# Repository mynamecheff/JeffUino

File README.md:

# Name In Progress
mcu board I'm making

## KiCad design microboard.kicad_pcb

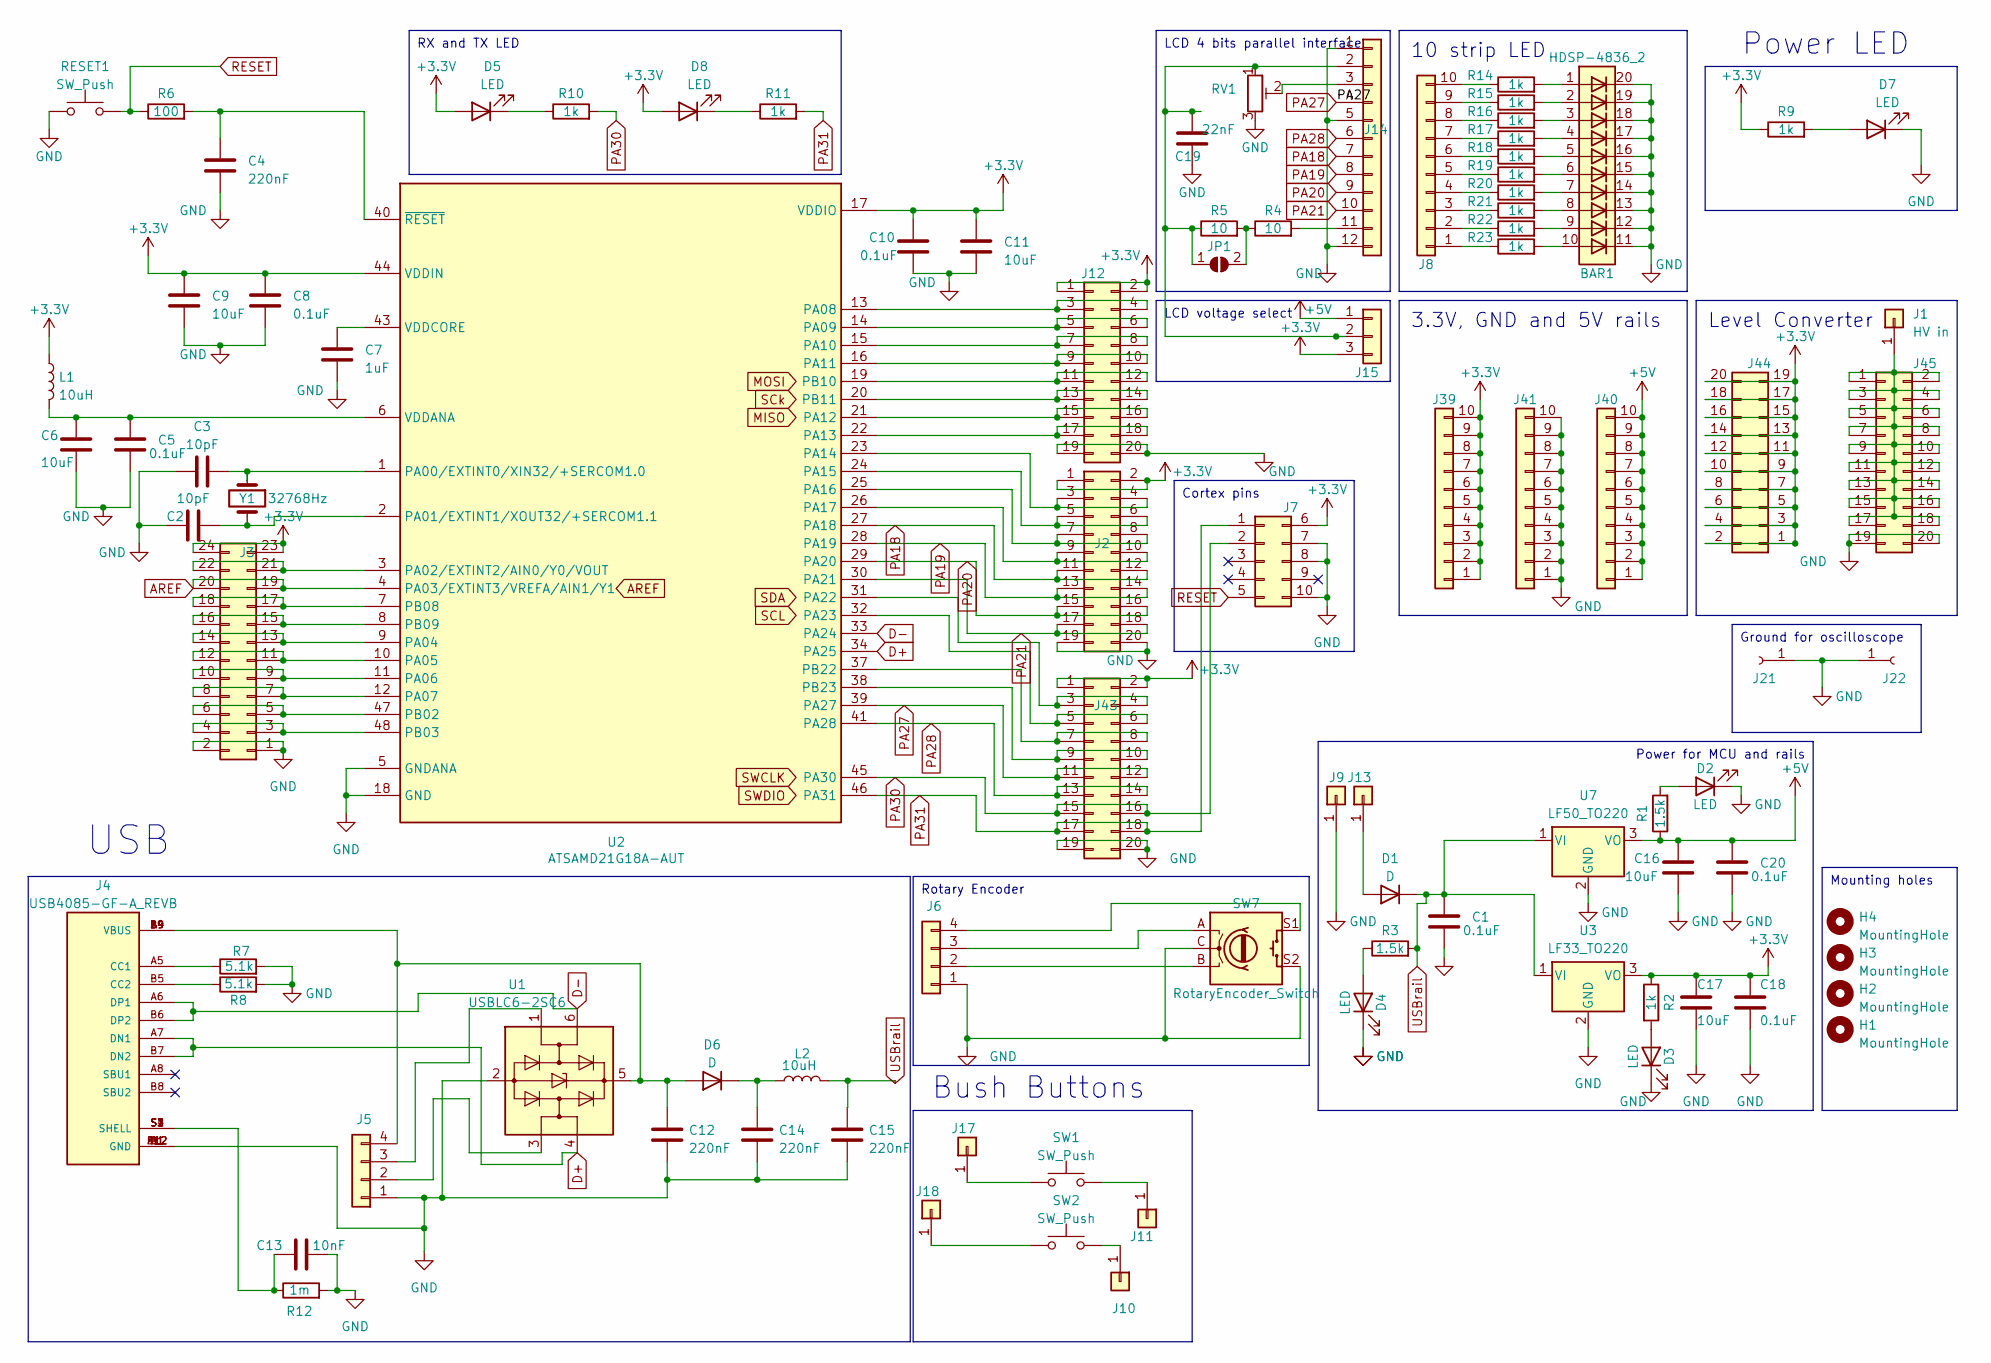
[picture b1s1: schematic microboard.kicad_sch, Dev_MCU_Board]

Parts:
BAR1: HDSP-4836_2; HDSP-4836
C1, C5, C8, C10, C18, C20: 0.1uF; C_0805_2012Metric_Pad1.18x1.45mm_HandSolder
C2, C3: 10pF; C_0805_2012Metric_Pad1.18x1.45mm_HandSolder
C4, C12, C14, C15: 220nF; C_0805_2012Metric_Pad1.18x1.45mm_HandSolder
C6, C9, C11, C16, C17: 10uF; C_0805_2012Metric_Pad1.18x1.45mm_HandSolder
C7: 1uF; C_0805_2012Metric_Pad1.18x1.45mm_HandSolder
C13: 10nF; C_0805_2012Metric_Pad1.18x1.45mm_HandSolder
C19: 22nF; C_0805_2012Metric_Pad1.18x1.45mm_HandSolder
D1, D6: D; D_SOD-323_HandSoldering
D2, D3, D4, D5, D7, D8: LED; LED_0805_2012Metric_Pad1.15x1.40mm_HandSolder
H1, H2, H3, H4: MountingHole; MountingHole_3.2mm_M3
J1: HV in; PinHeader_1x01_P2.54mm_Vertical
J2, J12: Conn_01x10; PinHeader_2x10_P2.54mm_Vertical
J3: Conn_02x12; PinHeader_2x12_P2.54mm_Vertical
J4: USB4085-GF-A_REVB; GCT_USB4085-GF-A_REVB; PARTREV B
J5, J6: Conn_01x04; PinHeader_1x04_P2.54mm_Vertical
J7: Conn_01x05; PinHeader_2x05_P1.27mm_Vertical
J8, J39, J40, J41: Conn_01x10; PinHeader_1x10_P2.54mm_Vertical
J9, J10, J11, J13, J17, J18: Conn_01x01; PinHeader_1x01_P2.54mm_Vertical
J14: Conn_01x12; PinHeader_1x12_P2.54mm_Vertical
J15: Conn_01x03; PinHeader_1x03_P2.54mm_Vertical
J21, J22: Conn_01x01_Socket; PinHeader_1x01_P2.54mm_Vertical
J43: Conn_01x05; PinHeader_2x10_P2.54mm_Vertical
J44: Conn_01x09; PinHeader_2x10_P2.54mm_Vertical
J45: Conn_01x08; PinHeader_2x10_P2.54mm_Vertical
JP1: SolderJumper_2_Open; SolderJumper-2_P1.3mm_Open_RoundedPad1.0x1.5mm
L1, L2: 10uH; L_0805_2012Metric_Pad1.05x1.20mm_HandSolder
R1, R3: 1.5k; R_0805_2012Metric_Pad1.20x1.40mm_HandSolder
R2, R9, R10, R11, R14, R15, R16, R17, R18, R19, R20, R21, R22, R23: 1k; R_0805_2012Metric_Pad1.20x1.40mm_HandSolder
R4, R5: 10; R_0805_2012Metric_Pad1.20x1.40mm_HandSolder
R6: 100; R_0805_2012Metric_Pad1.20x1.40mm_HandSolder
R7, R8: 5.1k; R_0805_2012Metric_Pad1.20x1.40mm_HandSolder
R12: 1m; R_0805_2012Metric_Pad1.20x1.40mm_HandSolder
RESET1: SW_Push; SW_PUSH_6mm_H8mm
RV1: R_Potentiometer_Trim; Potentiometer_Runtron_RM-065_Vertical
SW1, SW2: SW_Push; SW_PUSH_6mm_H8mm
SW7: RotaryEncoder_Switch; RotaryEncoder_Alps_EC11E-Switch_Vertical_H20mm
U1: USBLC6-2SC6; SOT-23-6
U2: ATSAMD21G18A-AUT; TQFP-48_7x7mm_P0.5mm_hand_solder; MPN ATSAMD21G18A-AUT
U3: LF33_TO220; TO-220-3_Vertical
U7: LF50_TO220; TO-220-3_Vertical
Y1: 32768Hz; Crystal_SMD_G8-2Pin_3.2x1.5mm_HandSoldering

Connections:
+3.3V: C8.1, C9.1, C10.1, C11.1, C17.1, C18.1, D5.2 (A), D8.2 (A), J2.1, J2.2, J3.23, J3.24, J7.6, J12.1, J12.2, J15.3, J39.1, J39.2, J39.3, J39.4, J39.5, J39.6, J39.7, J39.8, J39.9, J39.10, J43.1, J43.2, J44.1, J44.2, J44.3, J44.4, J44.5, J44.6, J44.7, J44.8, J44.9, J44.10, J44.11, J44.12, J44.13, J44.14, J44.15, J44.16, J44.17, J44.18, J44.19, J44.20, L1.1, R2.1, R9.1, U2.17 (VDDIO), U2.36 (VDDIO), U2.44 (VDDIN), U3.3 (VO); also elsewhere on the board
+5V: C16.1, C20.1, J15.1, J40.1, J40.2, J40.3, J40.4, J40.5, J40.6, J40.7, J40.8, J40.9, J40.10, R1.1, U7.3 (VO)
AREF: J3.19, J3.20, U2.4 (PA03/EXTINT3/VREFA/AIN1/Y1)
D+: J4.A7 (DN1), J4.B7 (DN2), U1.4 (I/O2), U2.34 (PA25)
D-: J4.A6 (DP1), J4.B6 (DP2), U1.6 (I/O1), U2.33 (PA24)
GND: BAR1.11 (K), BAR1.12 (K), BAR1.13 (K), BAR1.14 (K), BAR1.15 (K), BAR1.16 (K), BAR1.17 (K), BAR1.18 (K), BAR1.19 (K), BAR1.20 (K), C1.2, C2.1, C3.2, C4.2, C5.2, C6.2, C7.2, C8.2, C9.2, C10.2, C11.2, C12.2, C13.2, C14.2, C15.2, C16.2, C17.2, C18.2, C19.2, C20.2, D2.1 (K), D3.1 (K), D4.1 (K), D7.1 (K), J2.19, J2.20, J3.1, J3.2, J4.A1 (GND), J4.A12 (GND), J4.B1 (GND), J4.B12 (GND), J5.1, J6.1, J7.7, J7.8, J7.10, J9.1, J12.19, J12.20, J14.1, J14.5, J14.12, J21.1, J22.1, J41.1, J41.2, J41.3, J41.4, J41.5, J41.6, J41.7, J41.8, J41.9, J41.10, J43.19, J43.20, J45.19, J45.20, R7.2, R8.2, R12.2, RESET1.1, RV1.3, SW7.C, SW7.S2, U1.2 (GND), U2.5 (GNDANA), U2.18 (GND), U2.35 (GND), U2.42 (GND), U3.2 (GND), U7.2 (GND); also elsewhere on the board
unnamed: BAR1.1 (A), R14.2
unnamed: BAR1.2 (A), R15.2
unnamed: BAR1.3 (A), R16.2
unnamed: BAR1.4 (A), R17.2
unnamed: BAR1.5 (A), R18.2
unnamed: BAR1.6 (A), R19.2
unnamed: BAR1.7 (A), R20.2
unnamed: BAR1.8 (A), R21.2
unnamed: BAR1.9 (A), R22.2
unnamed: BAR1.10 (A), R23.2
unnamed: C13.1, J4.S1 (SHELL), J4.S2 (SHELL), J4.S3 (SHELL), J4.S4 (SHELL), R12.1
unnamed: D1.2 (A), J13.1
unnamed: D2.2 (A), R1.2
unnamed: D3.2 (A), R2.2
unnamed: D4.2 (A), R3.1
unnamed: D5.1 (K), R10.1
unnamed: C12.1, D6.2 (A), J4.A4 (VBUS), J4.A9 (VBUS), J4.B4 (VBUS), J4.B9 (VBUS), J5.4, U1.5 (VBUS)
unnamed: C14.1, D6.1 (K), L2.2
unnamed: D7.2 (A), R9.2
unnamed 26: D8.1 (K), R11.1; also elsewhere on the board
unnamed: J1.1, J45.1, J45.2, J45.3, J45.4, J45.5, J45.6, J45.7, J45.8, J45.9, J45.10, J45.11, J45.12, J45.13, J45.14, J45.15, J45.16, J45.17, J45.18
unnamed: J2.3, J2.4, U2.23 (PA14)
unnamed: J2.5, J2.6, U2.24 (PA15)
unnamed: J2.7, J2.8, U2.25 (PA16)
unnamed: J2.9, J2.10, U2.26 (PA17)
unnamed: J3.3, J3.4, U2.48 (PB03)
unnamed: J3.5, J3.6, U2.47 (PB02)
unnamed: J3.7, J3.8, U2.12 (PA07)
unnamed: J3.9, J3.10, U2.11 (PA06)
unnamed: J3.11, J3.12, U2.10 (PA05)
unnamed: J3.13, J3.14, U2.9 (PA04)
unnamed: J3.15, J3.16, U2.8 (PB09)
unnamed: J3.17, J3.18, U2.7 (PB08)
unnamed: J3.21, J3.22, U2.3 (PA02/EXTINT2/AIN0/Y0/VOUT)
unnamed: J4.A5 (CC1), R7.1
unnamed: J4.B5 (CC2), R8.1
unnamed: J5.2, U1.3 (I/O2)
unnamed: J5.3, U1.1 (I/O1)
unnamed: J6.2, SW7.B
unnamed: J6.3, SW7.A
unnamed: J6.4, SW7.S1
unnamed: J8.1, R23.1
unnamed: J8.2, R22.1
unnamed: J8.3, R21.1
unnamed: J8.4, R20.1
unnamed: J8.5, R19.1
unnamed: J8.6, R18.1
unnamed: J8.7, R17.1
unnamed: J8.8, R16.1
unnamed: J8.9, R15.1
unnamed: J8.10, R14.1
unnamed: J10.1, SW2.2
unnamed: J11.1, SW1.2
unnamed: J12.3, J12.4, U2.13 (PA08)
unnamed: J12.5, J12.6, U2.14 (PA09)
unnamed: J12.7, J12.8, U2.15 (PA10)
unnamed: J12.9, J12.10, U2.16 (PA11)
unnamed: J12.11, J12.12, U2.19 (PB10)
unnamed: J12.13, J12.14, U2.20 (PB11)
unnamed 66: J12.15, J12.16, U2.21 (PA12); also elsewhere on the board
unnamed: J12.17, J12.18, U2.22 (PA13)
unnamed: C19.1, J14.2, J15.2, JP1.1 (A), R5.1, RV1.1
unnamed: J14.3, RV1.2
unnamed: J14.11, R4.2
unnamed: J17.1, SW1.1
unnamed: J18.1, SW2.1
unnamed: J43.3, J43.4, U2.31 (PA22)
unnamed: J43.5, J43.6, U2.32 (PA23)
unnamed: J43.7, J43.8, U2.37 (PB22)
unnamed: J43.9, J43.10, U2.38 (PB23)
unnamed: JP1.2 (B), R4.1, R5.2
unnamed: C3.1, U2.1 (PA00/EXTINT0/XIN32/+SERCOM1.0), Y1.1
unnamed: C2.2, U2.2 (PA01/EXTINT1/XOUT32/+SERCOM1.1), Y1.2
unnamed: C5.1, C6.1, L1.2, U2.6 (VDDANA)
unnamed: C7.1, U2.43 (VDDCORE)
unnamed: C4.1, R6.2, U2.40 (~RESET)
PA18: J2.11, J2.12, J14.7, U2.27 (PA18)
PA19: J2.13, J2.14, J14.8, U2.28 (PA19)
PA20: J2.15, J2.16, J14.9, U2.29 (PA20)
PA21: J2.17, J2.18, J14.10, U2.30 (PA21)
PA27: J14.4, J43.11, J43.12, U2.39 (PA27)
PA28: J14.6, J43.13, J43.14, U2.41 (PA28)
PA30: J7.2, J43.15, J43.16, R10.2, U2.45 (PA30)
PA31: J7.1, J43.17, J43.18, R11.2, U2.46 (PA31)
RESET: J7.5, R6.1, RESET1.2
USBrail: C1.1, C15.1, D1.1 (K), L2.1, R3.2, U3.1 (VI), U7.1 (VI)

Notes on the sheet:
3.3V, GND and 5V rails
Rotary Encoder
LCD 4 bits parallel interface
LCD voltage select
Ground for oscilloscope
Mounting holes
Cortex pins
Power for MCU and rails
Level Converter
RX and TX LED
10 strip LED
Bush Buttons
Power LED
USB

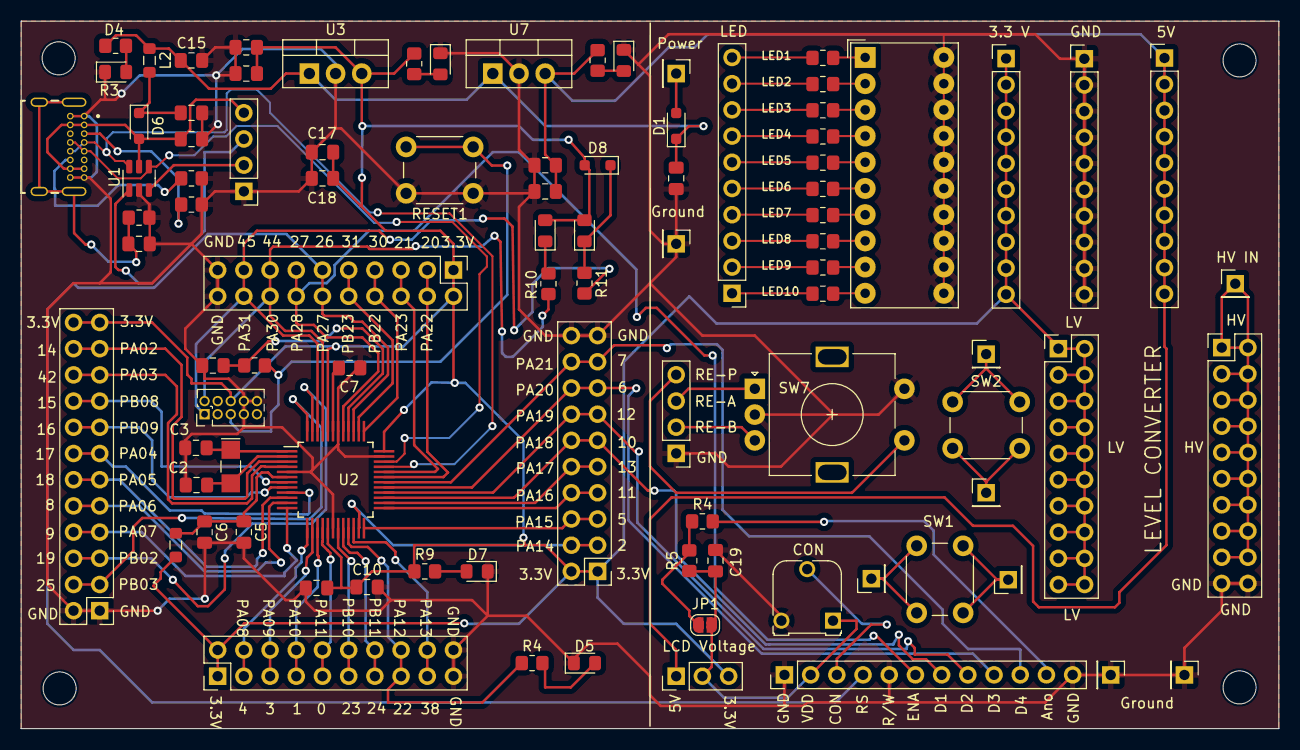
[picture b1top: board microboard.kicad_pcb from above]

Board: 2 copper layers, 121.9 x 68.6 mm, 96 parts (0 on the bottom side), 93 nets.

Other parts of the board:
D5#2, D8#2: LED; LED_0805_2012Metric_Pad1.15x1.40mm_HandSolder
R4#2: 1k; R_0805_2012Metric_Pad1.20x1.40mm_HandSolder

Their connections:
+3.3V: D8#2.2 (A); also elsewhere on the board
GND: D5#2.1 (K); also elsewhere on the board
unnamed: D5#2.2 (A), R4#2.2
unnamed 26: D8#2.1 (K); also elsewhere on the board
unnamed 66: R4#2.1; also elsewhere on the board

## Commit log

2023-04-25 started on footprints
2023-04-30 paths
2023-05-14 almost final design
2023-06-07 new update just dropped!
2023-06-08 moved oscilloscope location and added jp label
2023-06-08 small msg
2023-06-08 final?
